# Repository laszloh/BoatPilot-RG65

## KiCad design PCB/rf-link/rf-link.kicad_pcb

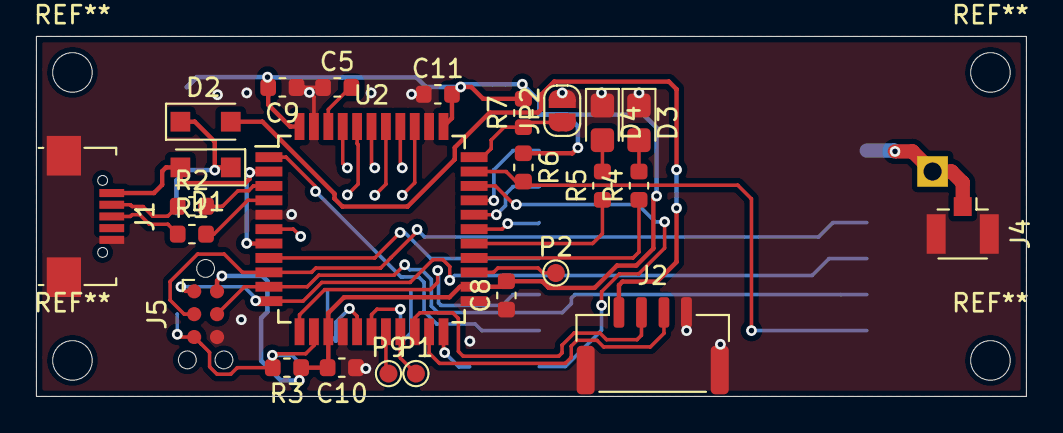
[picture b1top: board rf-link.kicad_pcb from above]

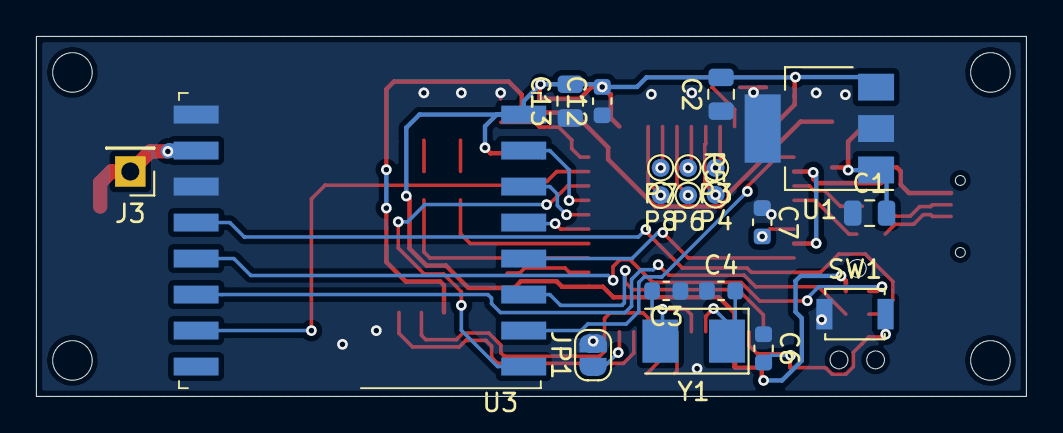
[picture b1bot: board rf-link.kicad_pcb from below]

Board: 2 copper layers, 55.0 x 20.0 mm, 45 parts (20 on the bottom side), 43 nets.

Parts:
C1, C2: 10u; C_0805_2012Metric
C3, C4: 22p; C_0603_1608Metric
C5, C6, C8, C9, C10, C11, C12: 100n; C_0603_1608Metric
C7: 1u; C_0603_1608Metric
C13: 1u; C_0805_2012Metric
D1, D2: SOT123; D_SOD-123F
D3: green; LED_0805_2012Metric_Castellated
D4: red; LED_0805_2012Metric_Castellated
J1: USB_A; USB_Micro-B_Futheda
J2: USART; JST_GH_SM04B-GHS-TB_1x04-1MP_P1.25mm_Horizontal
J3: ANT; PinHeader_1x01_P2.54mm_Vertical
J4: ANT; U.FL_Hirose_U.FL-R-SMT-1_Vertical
J5: AVR-ISP-6; Tag-Connect_TC2030-IDC-NL_2x03_P1.27mm_Vertical
JP1: Slave; SolderJumper-2_P1.3mm_Open_RoundedPad1.0x1.5mm
JP2: HWB; SolderJumper-2_P1.3mm_Open_RoundedPad1.0x1.5mm
P1, P2, P3, P4, P5, P6, P7, P8, P9: ICT-Point; TestPoint_Pad_D1.0mm
R1, R2: 22R; R_0603_1608Metric
R3, R4, R5, R6, R7: 10k; R_0603_1608Metric
SW1: reset; SW_SPST_B3U-1000P
U1: MCP1825S; SOT-223-3_TabPin2
U2: ATmega32U4-AU; TQFP-44_10x10mm_P0.8mm
U3: RFM69HW; HOPERF_RFM69HW
Y1: 8MHz; Crystal_SMD_5032-2Pin_5.0x3.2mm

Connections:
+3V3: C2.2, C8.2, C9.2, C10.2, C11.2, C12.2, C13.2, J5.2, R3.1, R6.1, R7.2, U1.3, U2.14, U2.24, U2.34, U2.44, U3.8
+5V: D2.2, J2.1
/ANT: J3.1, J4.1, U3.10
/D+: R1.2, U2.4
/D-: R2.2, U2.3
/DIO0: U2.1, U3.2
/DIO1: U2.12, U3.3
/DIO2: U2.8, U3.4
/DIO3: U2.28, U3.5
/DIO4: U2.29, U3.6
/DIO5: U2.30, U3.7
/LED_GREEN: R5.1, U2.27
/LED_RED: R4.1, U2.26
/MISO: J5.1, U2.11, U3.13
/MOSI: J5.4, U2.10, U3.14
/SCK: J5.3, U2.9, U3.12
/SLAVE: JP1.1, U2.22
/SS: R6.2, U2.32, U3.15
/UART1_RX: J2.2, U2.20
/UART1_TX: J2.3, U2.21
/USB_D+: J1.3, R1.1
/USB_D-: J1.2, R2.1
/Vsup: C1.2, D1.1, D2.1, U1.1
/~RFM_RST: U2.31, U3.1
/~RST: C6.2, J5.5, R3.2, SW1.2, U2.13
GND: C1.1, C2.1, C3.1, C4.1, C5.1, C6.1, C7.1, C8.1, C9.1, C10.1, C11.1, C12.1, C13.1, D3.1, D4.1, J1.5, J1.6, J2.4, J2.MP, J4.2, J5.6, JP1.2, JP2.2, SW1.1, U1.2, U2.5, U2.15, U2.23, U2.35, U2.43, U3.9, U3.11
unnamed: C3.2, U2.17, Y1.2
unnamed: C4.2, U2.16, Y1.1
unnamed: C5.2, U2.42
unnamed: C7.2, U2.6
unnamed: D3.2, R4.2
unnamed: D4.2, R5.2
unnamed: JP2.1, R7.1, U2.33
unnamed: P1.1, U2.19
unnamed: P2.1, U2.25
unnamed: P3.1, U2.41
unnamed: P4.1, U2.40
unnamed: P5.1, U2.39
unnamed: P6.1, U2.38
unnamed: P7.1, U2.37
unnamed: P8.1, U2.36
unnamed: P9.1, U2.18
VBUS: D1.2, J1.1, U2.2, U2.7

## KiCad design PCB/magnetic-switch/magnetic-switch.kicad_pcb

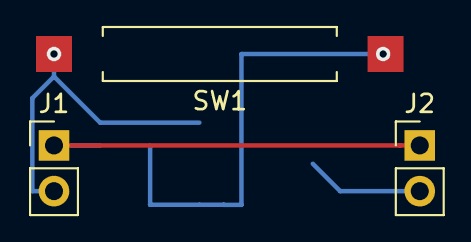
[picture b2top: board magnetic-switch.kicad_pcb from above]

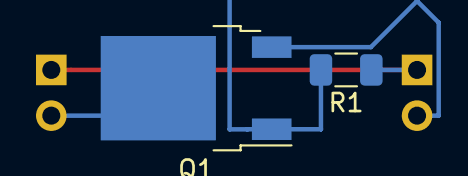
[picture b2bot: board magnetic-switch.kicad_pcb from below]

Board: 2 copper layers, 5 parts (2 on the bottom side), 4 nets.

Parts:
J1, J2: Conn_01x02; PinHeader_1x02_P2.54mm_Vertical
Q1: BUK7880-55A; TO-252-2
R1: 1M; R_1206_3216Metric
SW1: SW_Reed; SW_SPST_REED_CT10-XXXX-G2

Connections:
unnamed: J1.1, J2.1, R1.1
unnamed: J1.2, Q1.3, SW1.1
unnamed: J2.2, Q1.2
unnamed: Q1.1, R1.2, SW1.2

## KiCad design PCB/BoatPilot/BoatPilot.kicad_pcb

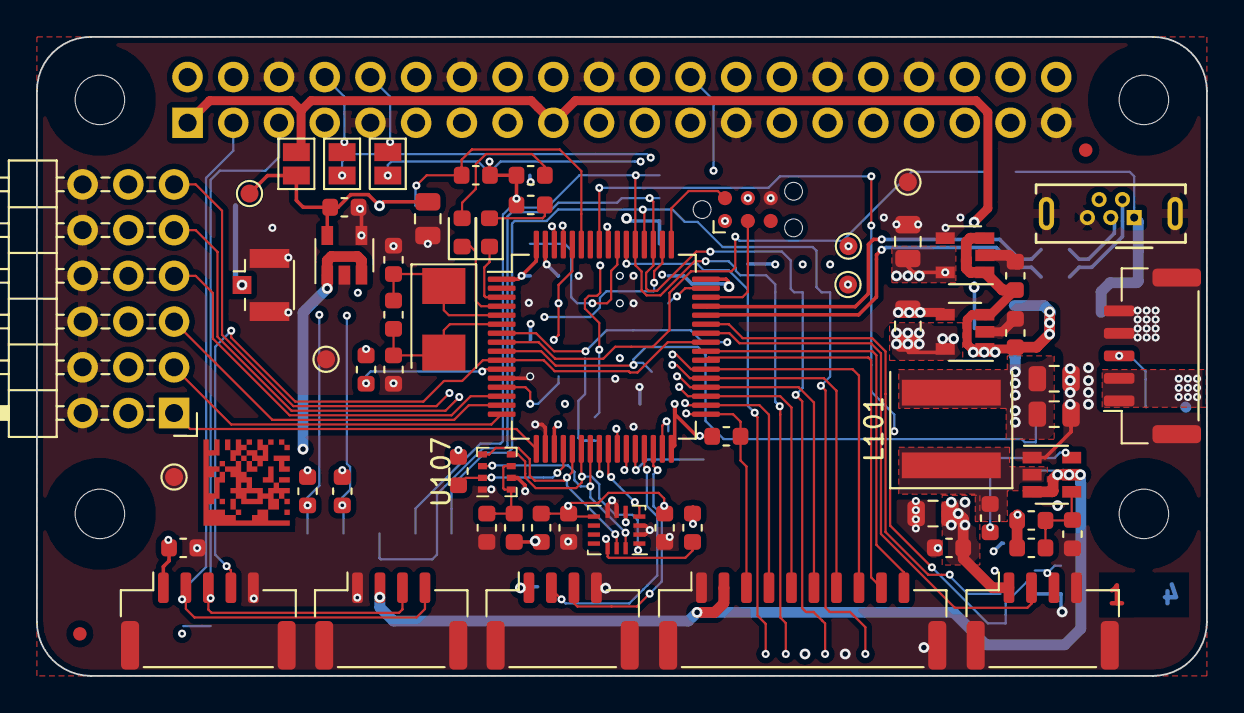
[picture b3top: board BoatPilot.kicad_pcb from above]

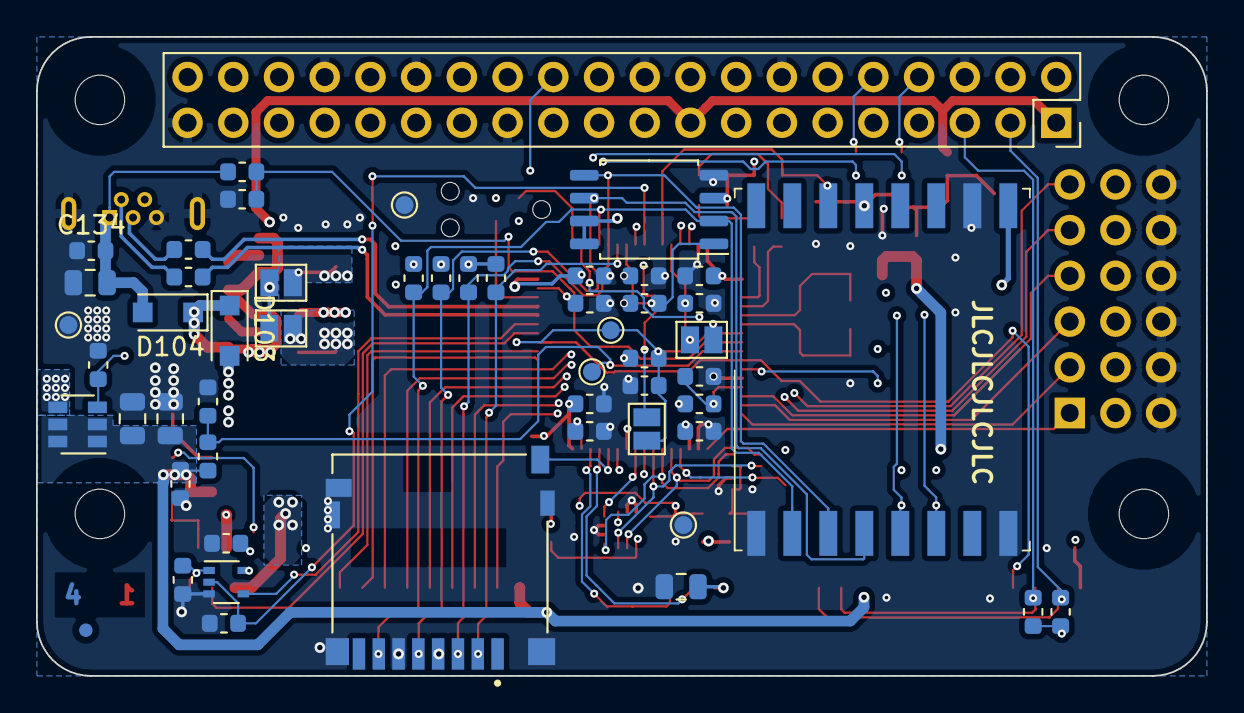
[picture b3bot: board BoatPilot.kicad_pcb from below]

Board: 4 copper layers, 65.0 x 35.5 mm, 118 parts (53 on the bottom side), 78 nets.

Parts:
Barcode**: BoatPilot
C101, C106, C109, C110, C112, C113, C114, C115, C116, C117, C119, C124, C125, C127, C129, C130, C131, C134: 100n; C_0603_1608Metric
C102, C105: 22u; C_0805_2012Metric
C103, C107, C108, C111, C126, C128, C132, C133: 10u; C_0805_2012Metric
C104, C118: 10n; C_0603_1608Metric
C120, C121: 2.2u; C_0603_1608Metric
C122, C123: 22p; C_0603_1608Metric
D101, D102: LED; LED_0603_1608Metric
D103, D104: PMEG3015EH,115; D_SOD-123F
FID101, FID102, FID103: Fiducial; Fiducial_0.75mm_Mask1.5mm
J101: battery; JST_GH_SM05B-GHS-TB_1x05-1MP_P1.25mm_Horizontal
J102: Raspberry_Pi_2_3; PinSocket_2x20_P2.54mm_Vertical
J103: FlexInput; JST_GH_SM10B-GHS-TB_1x10-1MP_P1.25mm_Horizontal
J104: Servo out; PinHeader_3x06_P2.54mm_Horizontal
J105: SWD; Tag-Connect_TC2030-IDC-NL_2x03_P1.27mm_Vertical
J108: UART; JST_GH_SM04B-GHS-TB_1x04-1MP_P1.25mm_Horizontal
J112: GPS; JST_GH_SM04B-GHS-TB_1x04-1MP_P1.25mm_Horizontal
J113: I2C; JST_GH_SM04B-GHS-TB_1x04-1MP_P1.25mm_Horizontal
J114: wind; JST_GH_SM05B-GHS-TB_1x05-1MP_P1.25mm_Horizontal
J115: ANT; U.FL_Hirose_U.FL-R-SMT-1_Vertical
J116: USB_OTG; USB_Micro-B_Wuerth_614105150721_Vertical
J117: Micro_SD_Card; AMPHENOL_1140084168
JP101: SBL; SolderJumper-2_P1.3mm_Open_Pad1.0x1.5mm
JP102, JP103, JP104: RPI 3.3V; SolderJumper-2_P1.3mm_Open_Pad1.0x1.5mm
JP105: RST; SolderJumper-2_P1.3mm_Open_Pad1.0x1.5mm
JP106: UART_TX; SolderJumper-2_P1.3mm_Open_Pad1.0x1.5mm
JP107: UART_RX; SolderJumper-2_P1.3mm_Open_Pad1.0x1.5mm
L101: XAL6030-332MEB; L_Coilcraft_XAL60xx_6.36x6.56mm
P101, P102, P104, P105, P106, P107, P108, P109, P110, P111, P112: ICT-Point; TestPoint_Pad_D1.0mm
Q101: TSM3457; SOT-23-6
R101, R105, R108, R120, R125: 47k; R_0603_1608Metric
R102, R104, R106, R107, R110, R112, R113, R114, R119, R121, R122, R127, R130, R133, R134, R135, R136: 10k; R_0603_1608Metric
R103: 54.9k; R_0603_1608Metric
R109, R111, R118: bead; L_0603_1608Metric
R115: 1M; R_0603_1608Metric
R116, R117, R123, R124: 2.2k; R_0603_1608Metric
R131, R132: 22R; R_0603_1608Metric
U101: TPS565208; SOT-23-6
U102, U103, U109: TLV75733PDBV; SOT-23-5
U104: BMX160; Bosch_LGA-14_3x2.5mm_P0.5mm
U105: STM32F405RGTx; LQFP-64_10x10mm_P0.5mm
U106: 74LVC1G86; SOT-353_SC-70-5
U107: BMP280; Bosch_LGA-8_2x2.5mm_P0.65mm_ClockwisePinNumbering
U108: W25Q128JVS; SOIC-8_5.23x5.23mm_P1.27mm
U111: RFM69HW; HOPERF_RFM69HW
Y101: 8MHz; Crystal_SMD_5032-2Pin_5.0x3.2mm

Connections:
+3.3VA: C111.2, JP104.1, P104.1, R111.2, R118.2, U103.5
+3.3VP: J102.1, J102.17, JP102.1, JP103.2, JP104.2
+3V3: C107.2, C112.2, C113.2, C114.2, C115.2, C124.2, C128.2, C129.2, C130.2, J105.1, J112.1, J114.1, J117.4, JP101.1, JP103.1, P101.1, R101.2, R107.1, R108.2, R109.2, R110.1, R112.1, R113.2, R116.2, R117.2, R119.1, R120.2, R123.2, R124.2, R125.2, R127.1, R130.1, R134.1, R136.2, U102.5, U105.1, U105.19, U105.32, U105.48, U105.64, U106.5, U108.3, U108.7, U108.8
+5V: C106.2, C110.2, C126.2, C127.2, D103.1, D104.1, J108.1, U102.1, U102.3, U103.1, U103.3, U109.1, U109.3
+5VP: C102.2, C104.2, C105.2, D103.2, J102.2, J102.4, J104.2, J104.5, J104.8, J104.11, J104.14, J104.17, L101.2, R103.1
+BATT: C103.2, C108.2, C109.1, J103.2, J113.2, Q101.1, Q101.2, Q101.5, Q101.6, R102.2, U101.3, U101.5
/5V_SENSE: R107.2, U105.11
/BMX160_INT1: U104.4, U105.25
/CARD_DET: J117.9, U105.28
/I2C1_SCL: J102.5, J113.3, J114.3, R123.1, U105.61
/I2C1_SDA: J102.3, J113.4, J114.2, R124.1, U105.62
/LED_STAT: D102.1, U105.3
/LED_WARN: D101.1, U105.4
/RFM_RST: R134.2, U105.56, U111.6
/RFM_SUP: C131.2, C132.2, JP102.2, P112.1, U109.5, U111.13
/SERVO_OUT1: J104.16, U105.26
/SERVO_OUT2: J104.13, U105.27
/SERVO_OUT3: J104.10, U105.14
/SERVO_OUT4: J104.7, U105.15
/SERVO_OUT5: J104.4, U105.16
/SERVO_OUT6: J104.1, U105.17
/SPI1_MISO: U104.1, U105.22, U107.5
/SPI1_MOSI: U104.14, U105.23, U107.3
/SPI1_SCK: U104.13, U105.21, U107.4
/SPI2_CS: J102.24, J103.3, R110.2, U105.33
/SPI2_MISO: J102.21, J103.5, U105.35
/SPI2_MOSI: J102.19, J103.6, U105.36
/SPI2_SCK: J102.23, J103.4, U105.34
/SPI3_MISO: J117.7, R101.1, U105.52, U108.2, U111.2
/SPI3_MOSI: J117.3, R120.1, U105.53, U108.5, U111.3
/SPI3_SCK: J117.5, R108.1, U105.51, U108.6, U111.4
/SYS_SWCLK: J105.2, U105.49
/SYS_SWDIO: J105.3, U105.46
/TIM8_CH3: J103.9, U105.39
/TIM8_CH4: J103.10, U105.40
/UART1_RX: U105.43, U106.4
/UART1_TX: J108.2, U105.42
/UART3_RX: J112.3, U105.30
/UART3_TX: J112.2, U105.29
/UART6_RX: J103.8, JP106.2, U105.38
/UART6_TX: J103.7, JP107.2, U105.37
/UART_INV: R122.2, U105.57, U106.2
/UART_RX: J108.3, R121.2, U106.1
/UBATT: P102.1, R102.1, R104.2, U105.9
/USBD+: J116.3, R131.1
/USBD-: J116.2, R132.1
/USB_N: R132.2, U105.44
/USB_P: R131.2, U105.45
/VBUS_SENSE: R133.1, R135.2, U105.8
/WIND_PWM: J114.4, U105.10, U105.41
/~CS_BMP280: R119.2, U105.20, U107.2
/~CS_BMX160: R112.2, U104.12, U105.24
/~CS_FLASH: R127.2, U105.55, U108.1
/~CS_RFM69: R130.2, U105.50, U111.5
/~CS_SDCARD: J117.2, R125.1, U105.54
/~RFM69_IRQ: R136.1, U105.59, U111.14
/~RST: C119.2, J105.4, JP105.2, P111.1, R113.1, U105.7
GND: C102.1, C103.1, C105.1, C106.1, C107.1, C108.1, C109.2, C110.1, C111.1, C112.1, C113.1, C114.1, C115.1, C116.1, C117.1, C118.1, C119.1, C120.1, C121.1, C122.1, C123.1, C124.1, C125.1, C126.1, C127.1, C128.1, C129.1, C130.1, C131.1, C132.1, C133.1, C134.1, J101.4, J101.5, J101.MP, J102.6, J102.9, J102.14, J102.20, J102.25, J102.30, J102.34, J102.39, J103.1, J103.MP, J104.3, J104.6, J104.9, J104.12, J104.15, J104.18, J105.6, J108.4, J108.MP, J112.4, J112.MP, J113.1, J113.MP, J114.5, J114.MP, J115.2, J116.5, J116.6, J117.6, J117.10, J117.11, P105.1, P106.1, P107.1, P108.1, P109.1, P110.1, R104.1, R105.1, R106.1, R114.1, R121.1, R122.1, R135.1, U101.1, U102.2, U102.4, U103.2, U103.4, U104.2, U104.3, U104.6, U104.7, U105.12, U105.18, U105.63, U106.3, U107.1, U107.7, U108.4, U109.2, U109.4, U111.1, U111.8, U111.10
unnamed: C101.1, U101.6
unnamed: C101.2, L101.1, U101.2
unnamed: C104.1, R103.2, R106.2, U101.4
unnamed: C116.2, R109.1, U105.13
unnamed: C117.2, C118.2, R111.1, U104.5, U104.8
unnamed: C120.2, U105.31
unnamed: C121.2, U105.47
unnamed: C122.2, R115.1, U105.5, Y101.1
unnamed: C123.2, R115.2, U105.6, Y101.2
unnamed: C125.2, R118.1, U107.6, U107.8
unnamed: D101.2, R116.1
unnamed: D102.2, R117.1
unnamed: J101.1, J101.2, Q101.4
unnamed: J101.3, Q101.3, R105.2
unnamed: J102.8, JP106.1
unnamed: J102.10, JP107.1
unnamed: J102.15, JP105.1
unnamed: J115.1, U111.9
unnamed: JP101.2, R114.2, U105.60
VBUS: C133.2, C134.2, D104.2, J116.1, R133.2

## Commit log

2020-06-17 Squashed commit of the following:
    commit f1388340b592fd14a4ec46a5619306b7a5938473
    Author: Laszlo Hegedues <laszlo.hegedues@gmail.com>
    Date: Tue Jun 16 11:28:14 2020 +0200
    First Layout finished
    9-axis accel is still not positioned in the best way
    commit 5897b2db92ea9f9b20543b0505b5d895ee9b1003
2020-06-17 Add step-down to schematic and start layout
    Step-Down is now included in the schematic. Placement of the parts has
    started.
2020-06-17 Layout update
2020-06-18 Entflechtung geht weiter
2020-06-19 Layout Version 1 with MP1854 finished
2020-06-19 Update the step down to TPS
2020-06-22 Add missing vias
    100% layout finished. CHecks still open
2020-06-22 Fabrication layer cleanup
    Started to clean up fabrication layer output since there will be no silk
    screen printed for this project
2020-06-23 Finish documentation
    Documentation layer finished
2020-06-23 Start SW implementation for the STM32
    Add some test files to verify everything'll work as planned.
2020-06-23 Move Servo outputs
    Move servo outputs so that only a single Timer (TIM2) is needed to
    gerenarte the PWM with the Capture Compare units.
2020-06-23 Route new servo connections
    Reroute parts of the PCB to fit the new servo connections
2020-06-25 Swap UART1 RX and TX to enable half duplex mode
    In half duplex mode, UART RX can be used as a GPIO pin. So the pinning
    on the uC has to be swapped.
2020-06-25 software configuration
2020-06-26 test-software preparation
2020-06-30 Add test points for a software serial port
    Update the layout to have a SW UART (3,3V, TX, RX, GND)
2020-06-30 Work in progress on the test code
2020-06-30 Create the arduino basic code
2020-07-01 SW in Work
2020-07-01 All needed Modules are added
2020-07-01 Add 3D models for mechanical testings
2020-07-02 Add heatpads for the voltage regulators to the layout
2020-07-08 Add DMC to project
2020-07-09 Update layout
    Change the LM1117 to a smaller sized LDO and adapt the layout.
2020-07-09 Library updates
2020-07-10 Add USB pull-up resistor and connector
    Add the missing pull-up resistors to the USB line and add a mini-usb
    header to the board
2020-07-13 Fix DRC errors and optimise USB lines
    Fix the DRC errors and remove the strip lines from the USB data lines.
2020-07-15 Readd eeporm chip
    The eeprom was deleted and the SOIC was added to the layout again
2020-07-15 Further optimize layout
    Clean up the layout a bit further
2020-07-15 Update 3D models and create the assembly
    There seems to be a missmatch between the 3D model fo the 9-axis gyro
    and the PCB footprint.
    ToDo: Check if the model of the 9-axis gyro or the foot print is wrong.
2020-07-16 Fix the standoffs
    Fix the standoffs and prepare them for 3d printing
2020-07-16 Shift decoupling capacitor out of eeprom IC
    The capacitor was colliding with it's IC. This commit fixes the problem
2020-07-16 Prepare layout for 4 layer PCB
    Prepare the board for 4 layer PCB to incorporate the the 10-axis
    IMU into the PCB.
2020-07-17 Start the high desity schematics and layout
    Start the design of the high density layout with a maximum of 4 layers
2020-07-18 Layout rework
2020-08-17 Add reference documents for arudpilot support
    Add reference to the open source ardupliot used and start the schematic rework based on the OpenPilot Revolution board to add as much synergies as possible (reducing SW overhead).
2020-08-19 Start the layout with the Raspberry Pi W header
2020-08-20 Work on the layout
2020-08-21 Working on the layout
2020-08-21 Routing in work
    nightly commit
2020-08-23 Layout in work
2020-08-24 Add DMC code and clean layout
2020-08-24 Further layout work
2020-08-27 Layout cleanup
2020-08-30 Layout review and cleanup, silkscreen cleanup
2020-08-31 Fix fail wit GPS connector not being attached to the uC
2020-08-31 Fix blunder in layout
2020-09-02 Update submodules
2020-09-02 Add BMP280 to the layout
2020-09-04 Remove orig file from merge
2020-09-07 Fix Coil footprint and add 3x06 pin header from Samtec
2020-09-08 Layout and schematic optimisations
2020-09-09 Prepare for production
2020-09-22 Add mounts for WIng FC-10, RC and GPS moudle stack
2020-09-23 Working on it
2020-09-28 Add new project for the RF-Link GCS part
2020-10-05 add stuff
2020-10-06 Work on the rf-link usb module
2020-10-06 Add RFM69 Software system
